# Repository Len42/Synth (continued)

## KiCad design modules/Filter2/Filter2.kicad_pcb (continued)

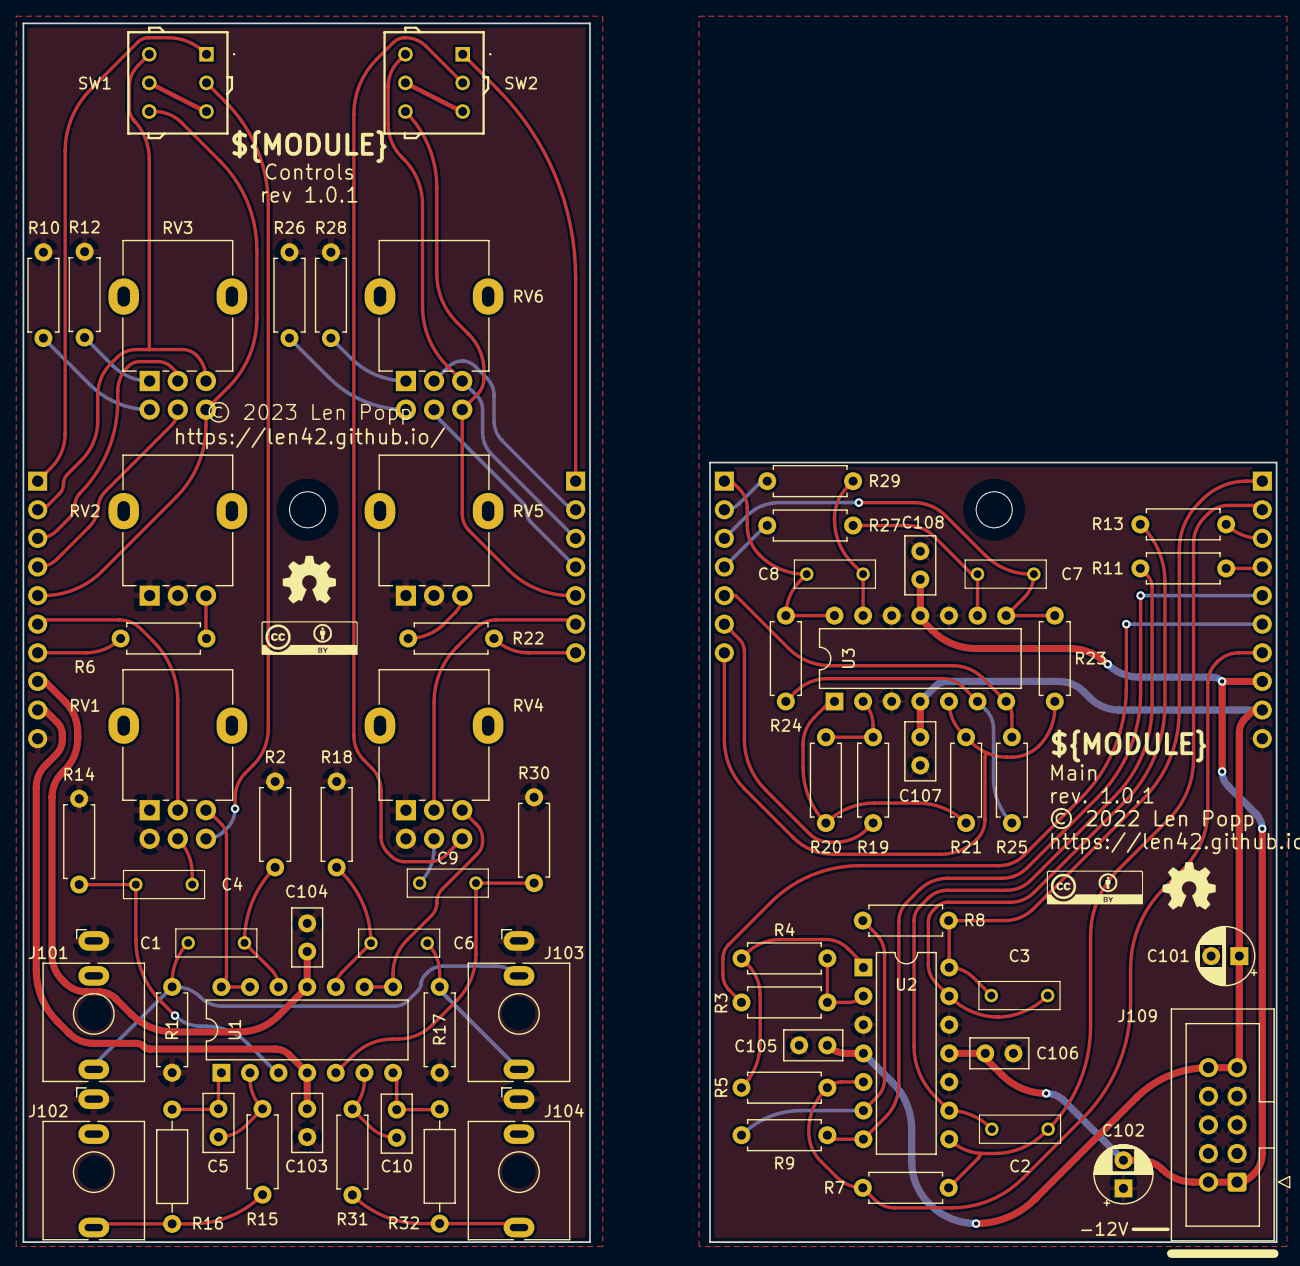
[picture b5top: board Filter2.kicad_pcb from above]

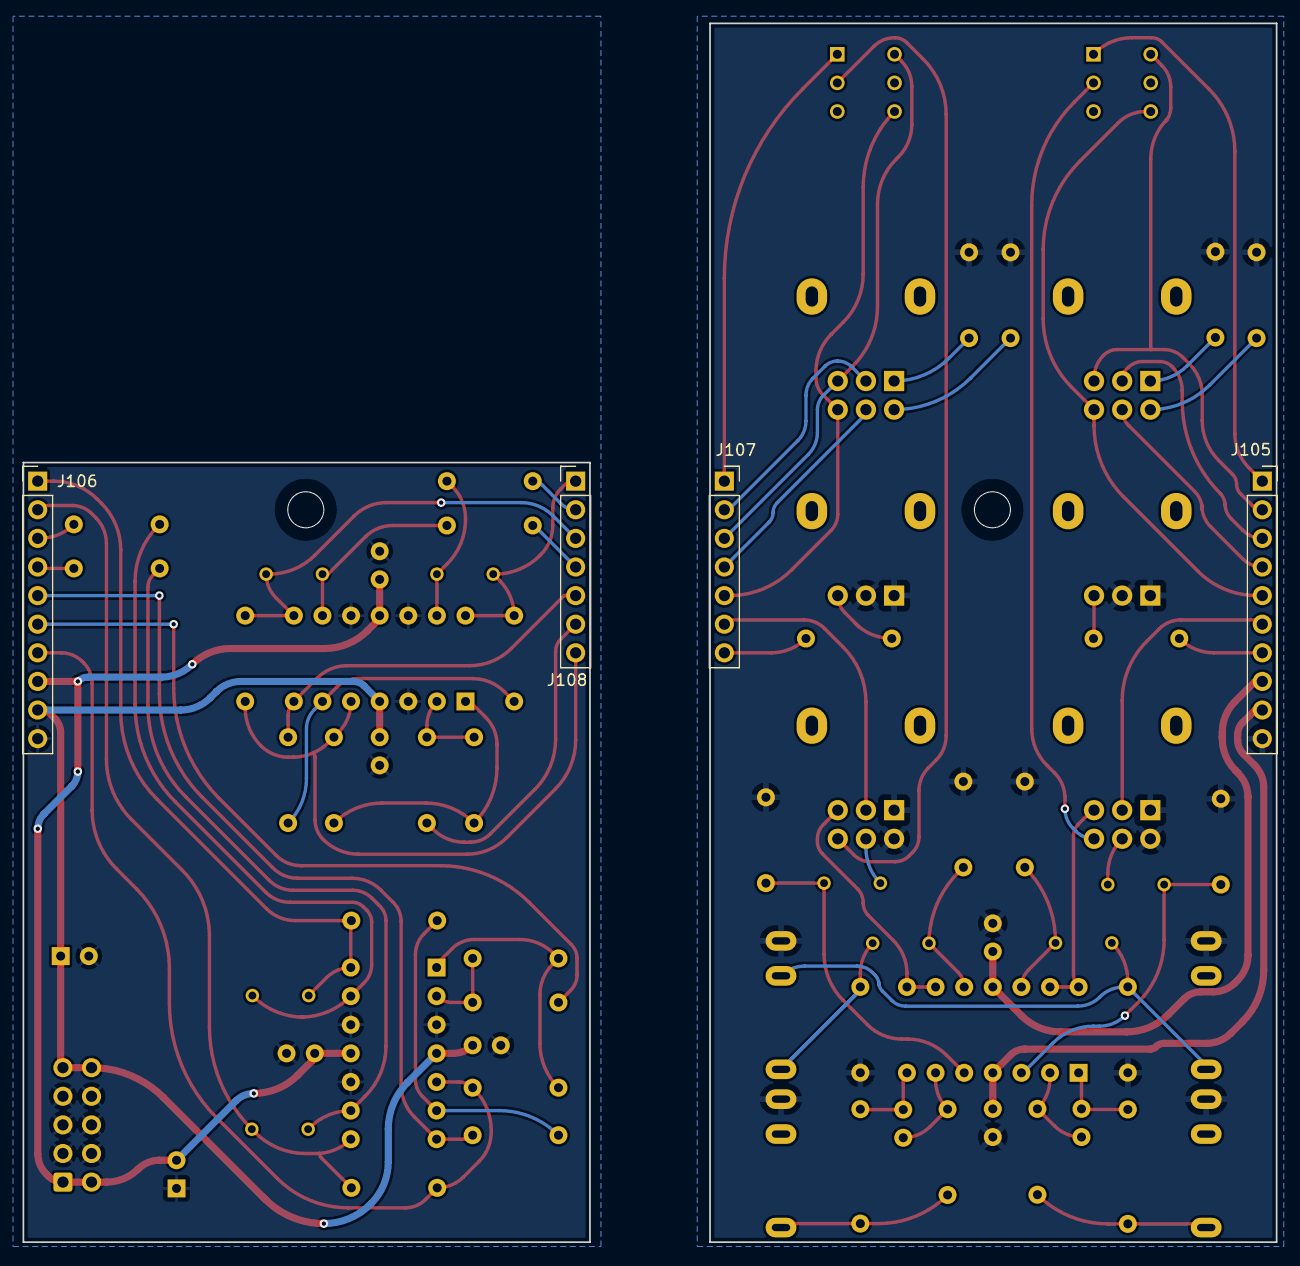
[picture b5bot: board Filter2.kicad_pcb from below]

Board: 2 copper layers, 111.3 x 108.2 mm, 76 parts (4 on the bottom side), 51 nets.

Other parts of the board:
G1, G2: Logo_CC_BY
G3, G4: Logo_OSHW

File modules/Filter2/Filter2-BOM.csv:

Ref,Qty,Value,Value2,Note,Description,Datasheet,Manufacturer,ManuPartNum,Distributor1,DistributorPartNum1,DistributorPartLink1,Distributor2,DistributorPartNum2,DistributorPartLink2,Distributor3,DistributorPartNum3,DistributorPartLink3
"A101","1","Cable_Eurorack_10","","Length as required","Eurorack 16-10 pin power cable","","","","Thonk","","https://www.thonk.co.uk/shop/eurorack-power-cables/","SynthCube","","https://synthcube.com/cart/eurorack-ribbon-power-cables","Modular Addict","","https://modularaddict.com/parts/eurorack-power-cables-1"
"C1 C4 C6 C9","4","1U","","","Capacitor - Film","https://www.mouser.ca/datasheet/2/447/KEM_F3101_R82-3316969.pdf","KEMET","R82DC4100AA60K","Mouser","80-R82DC4100AA60K","https://www.mouser.ca/ProductDetail/KEMET/R82DC4100AA60K?qs=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","","","","","",""
"C2 C3 C7 C8","4","2N2","","","Capacitor - Film","https://www.mouser.ca/datasheet/2/447/F3294_MMK-3316041.pdf","KEMET","MMK5222J100J01L16.5TA18","Mouser","80-MMK5222J100J1TA18","https://www.mouser.ca/ProductDetail/KEMET/MMK5222J100J01L16.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","","","","","",""
"C5 C10","2","22P","C0G","","Capacitor - Ceramic","https://product.tdk.com/system/files/dam/doc/product/capacit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","TDK","FG18C0G1H220JNT00","Mouser","810-FG18C0G1H220JNT0","https://www.mouser.ca/ProductDetail/TDK/FG18C0G1H220JNT00?qs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","","","","","",""
"C101 C102","2","10U","35 VDC","12 V decoupling","Capacitor - Electrolytic - 12 V decoupling","https://www.mouser.ca/datasheet/2/315/ABA0000C1059-947582.pdf","Panasonic","ECE-A1VKS100I","Mouser","667-ECE-A1VKS100I","https://www.mouser.ca/ProductDetail/667-ECE-A1VKS100I","Thonk","Group_Eurorack_DIY_Essential","https://www.thonk.co.uk/shop/eurorack-diy-essentials/","","",""
"C103 C104 C105 C106 C107 C108","6","100N","","IC decoupling","Capacitor - Ceramic - IC decoupling","https://product.tdk.com/system/files/dam/doc/product/capacit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","TDK","FG18X7R1H104KNT06","Mouser","810-FG18X7R1H104KNT6","https://www.mouser.ca/ProductDetail/810-FG18X7R1H104KNT6","","","","","",""
"H101 H105","2","HW_Screw_M3x0.50x6","","","Machine screw, M3x0.50x6","","","","","","","","","","","",""
"H103","1","HW_Standoff_F-F_11mm_M3x0.50","","","Standoff, 11mm, female-female, M3x0.50","https://www.thonk.co.uk/wp-content/uploads/2018/05/standoff-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","Ettinger","05.03.111","Thonk","Mech_11mm_Standoff_(x10)","https://www.thonk.co.uk/shop/standoffs/","Mouser","710-970110321","https://www.mouser.ca/ProductDetail/Wurth-Elektronik/9701103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","Mouser","144-MTS-11","https://www.mouser.ca/ProductDetail/144-MTS-11"
"J101 J102 J103 J104","4","WQP-PJ398","","","Audio Jack, 2 Poles (Mono / TS), Switched T Pole (Normalling), QingPu / Thonkiconn","http://www.qingpu-electronics.com/en/products/WQP-PJ398SM-362.html","QingPu / Thonk","PJ398SM / WQP518MA","Thonk","PJ398SM","https://www.thonk.co.uk/shop/thonkiconn/","SynthCube","WQP518MA","https://synthcube.com/cart/3-5mm-euro-jacks","Adafruit","4031","https://www.adafruit.com/product/4031"
"J105","1","Conn_Front_Left_Top","","","Generic connector, single row, 01x10, script generated (kicad-library-utils/schlib/autogen/connector/)","","","","Adafruit","598","https://www.adafruit.com/product/598","Mouser","710-61303211821","https://www.mouser.ca/ProductDetail/Wurth-Elektronik/6130321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","","",""
"J106","1","Conn_Back_Right_Top","","","Generic connector, single row, 01x10, script generated (kicad-library-utils/schlib/autogen/connector/)","","","","Adafruit","392","https://www.adafruit.com/product/392","Mouser","649-1012937893601BLF","https://www.mouser.ca/ProductDetail/649-1012937893601BLF","","",""
"J107","1","Conn_Front_Right","","","Generic connector, single row, 01x07, script generated (kicad-library-utils/schlib/autogen/connector/)","","","","Adafruit","598","https://www.adafruit.com/product/598","Mouser","710-61303211821","https://www.mouser.ca/ProductDetail/Wurth-Elektronik/6130321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","","",""
"J108","1","Conn_Back_Left","","","Generic connector, single row, 01x07, script generated (kicad-library-utils/schlib/autogen/connector/)","","","","Adafruit","392","https://www.adafruit.com/product/392","Mouser","649-1012937893601BLF","https://www.mouser.ca/ProductDetail/649-1012937893601BLF","","",""
"J109","1","Conn_Eurorack_10","","","Eurorack 10-pin board power connector","https://www.mouser.ca/datasheet/2/445/61201021621-1717731.pdf","Wurth Elektronik","61201021621","Mouser","710-61201021621","https://www.mouser.ca/ProductDetail/Wurth-Elektronik/6120102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","Thonk","","https://www.thonk.co.uk/shop/eurorack-diy-essentials/","","",""
"R1 R14 R17 R30","4","1M","1%, 1/6 W","","Resistor","https://www.mouser.ca/datasheet/2/447/YAGEO_MFR_datasheet_20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","YAGEO","MFR-12FTF52-1M","Mouser","603-MFR-12FTF52-1M","https://www.mouser.ca/ProductDetail/YAGEO/MFR-12FTF52-1M?qs=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","","","","","",""
"R2 R15 R18 R31","4","100K","1%, 1/6 W","","Resistor","https://www.mouser.ca/datasheet/2/447/YAGEO_MFR_datasheet_20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","YAGEO","MFR-12FTF52-100K","Mouser","603-MFR-12FTF52-100K","https://www.mouser.ca/ProductDetail/YAGEO/MFR-12FTF52-100K?q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","","","","","",""
"R3 R7 R11 R13 R19 R23 R27 R29","8","10K","1%, 1/6 W","","Resistor","https://www.mouser.ca/datasheet/2/447/YAGEO_MFR_datasheet_20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","YAGEO","MFR-12FTF52-10K","Mouser","603-MFR-12FTF52-10K","https://www.mouser.ca/ProductDetail/YAGEO/MFR-12FTF52-10K?qs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","","","","","",""
"R4 R5 R20 R21","4","22K","1%, 1/6 W","","Resistor","https://www.mouser.ca/datasheet/2/447/YAGEO_MFR_datasheet_20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","YAGEO","MFR-12FTF52-22K","Mouser","603-MFR-12FTF52-22K","https://www.mouser.ca/ProductDetail/YAGEO/MFR-12FTF52-22K?qs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","","","","","",""
"R6 R22","2","1K","1%, 1/6 W","","Resistor","https://www.mouser.ca/datasheet/2/447/YAGEO_MFR_datasheet_20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","YAGEO","MFR-12FTF52-1K","Mouser","603-MFR-12FTF52-1K","https://www.mouser.ca/ProductDetail/YAGEO/MFR-12FTF52-1K?qs=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","","","","","",""
"R8 R9 R24 R25","4","15K","1%, 1/6 W","","Resistor","https://www.mouser.ca/datasheet/2/447/YAGEO_MFR_datasheet_20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","YAGEO","MFR-12FTF52-15K","Mouser","603-MFR-12FTF52-15K","https://www.mouser.ca/ProductDetail/YAGEO/MFR-12FTF52-15K?qs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","","","","","",""
"R10 R12 R26 R28","4","68R","1%, 1/6 W","","Resistor","https://www.mouser.ca/datasheet/2/447/YAGEO_MFR_datasheet_20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","YAGEO","MFR-12FTF52-68R","Mouser","603-MFR-12FTF52-68R","https://www.mouser.ca/ProductDetail/YAGEO/MFR-12FTF52-68R?qs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","","","","","",""
"R16 R32","2","51R","1%, 1/4 W","Output limiting","Resistor","https://www.mouser.ca/datasheet/2/447/Yageo_LR_MFR_1-1714151.pdf","YAGEO","MFR-25FBF52-51R","Mouser","603-MFR-25FBF52-51R","https://www.mouser.ca/ProductDetail/?qs=oAGoVhmvjhzVx2bdEH1T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","","","","","",""
"RV1 RV4","2","50K","LOG","","Dual potentiometer, separate units","https://www.thonk.co.uk/wp-content/uploads/Documents/alpha/9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","Alpha","RD902F-*","Thonk","Group_Pot_Alpha_6.35mm","https://www.thonk.co.uk/shop/alpha-9mm-pots/","","","","","",""
"RV2 RV5","2","50K","LOG","","Potentiometer","https://www.mouser.ca/datasheet/2/13/alpha_taiwan_08192019_R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","Alpha","RD901F-*","Thonk","Group_Pot_Alpha_6.35mm","https://www.thonk.co.uk/shop/alpha-9mm-pots/","","","","","",""
"RV3 RV6","2","10K","LOG","","Dual potentiometer, separate units","https://www.thonk.co.uk/wp-content/uploads/Documents/alpha/9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","Alpha","RD902F-*","Thonk","Group_Pot_Alpha_6.35mm","https://www.thonk.co.uk/shop/alpha-9mm-pots/","","","","","",""
"SW1 SW2","2","SW_SP3T","","Pins 3 & 5 must be connected","Toggle Switch, three position, single pole triple throw, 3 position switch, SP3T, ON-ON-ON, NKK A24JP","https://www.nkkswitches.com/pdf/Atoggles.pdf","NKK","A24JP","Mouser","633-A24JP","https://www.mouser.ca/ProductDetail/NKK-Switches/A24JP?qs=44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","DigiKey","360-3408-ND","https://www.digikey.ca/en/products/detail/nkk-switches/A24JP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","","",""
"U1 U2 U3","3","TL074","","","Quad Low-Noise JFET-Input Operational Amplifiers, DIP-14/SOIC-14","http://www.ti.com/lit/ds/symlink/tl071.pdf","Texas Instruments","TL074BCN","Mouser","595-TL074BCN","https://www.mouser.ca/ProductDetail/?qs=vxEfx8VrU7BHurOY5iQd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","","","","","",""

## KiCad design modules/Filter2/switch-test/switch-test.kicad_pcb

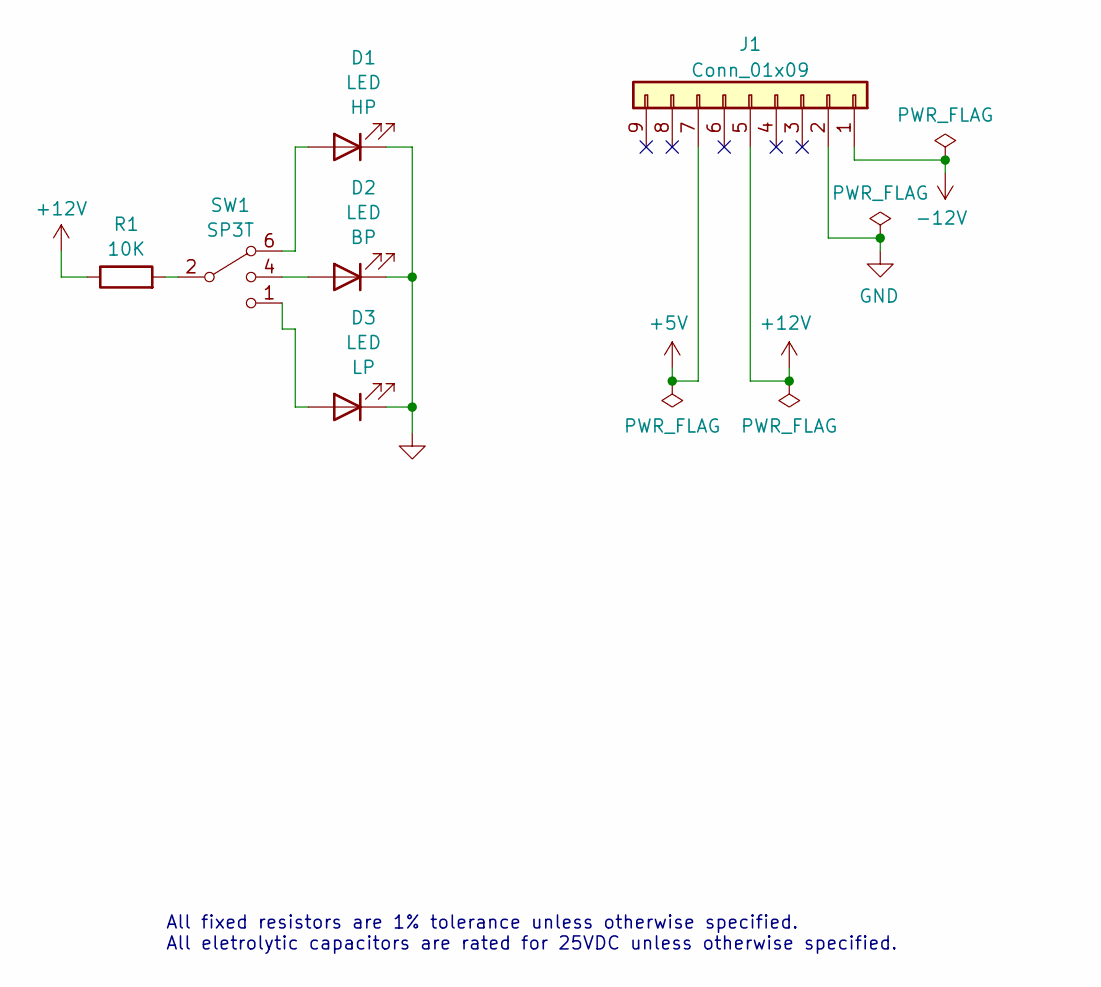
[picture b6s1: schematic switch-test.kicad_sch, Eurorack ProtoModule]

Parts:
D1, D2, D3: LED; LED_D3.0mm_Clear
J1: Conn_01x09; PinHeader_1x09_P2.54mm_Vertical
R1: 10K; SB_Gen_1; ManufacturerPartNum MFR-12*
SW1: SP3T; SW_SP3T_A24JP; ManufacturerPartNum A24JP

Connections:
+5V: J1.7
+12V: J1.5, R1.1
-12V: J1.1
GND: D1.1 (K), D2.1 (K), D3.1 (K), J1.2
unnamed: D1.2 (A), SW1.6
unnamed: D2.2 (A), SW1.4
unnamed: D3.2 (A), SW1.1
unnamed: R1.2, SW1.2

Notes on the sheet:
All fixed resistors are 1% tolerance unless otherwise specified. All eletrolytic capacitors are rated for 25VDC unless otherwise specified.

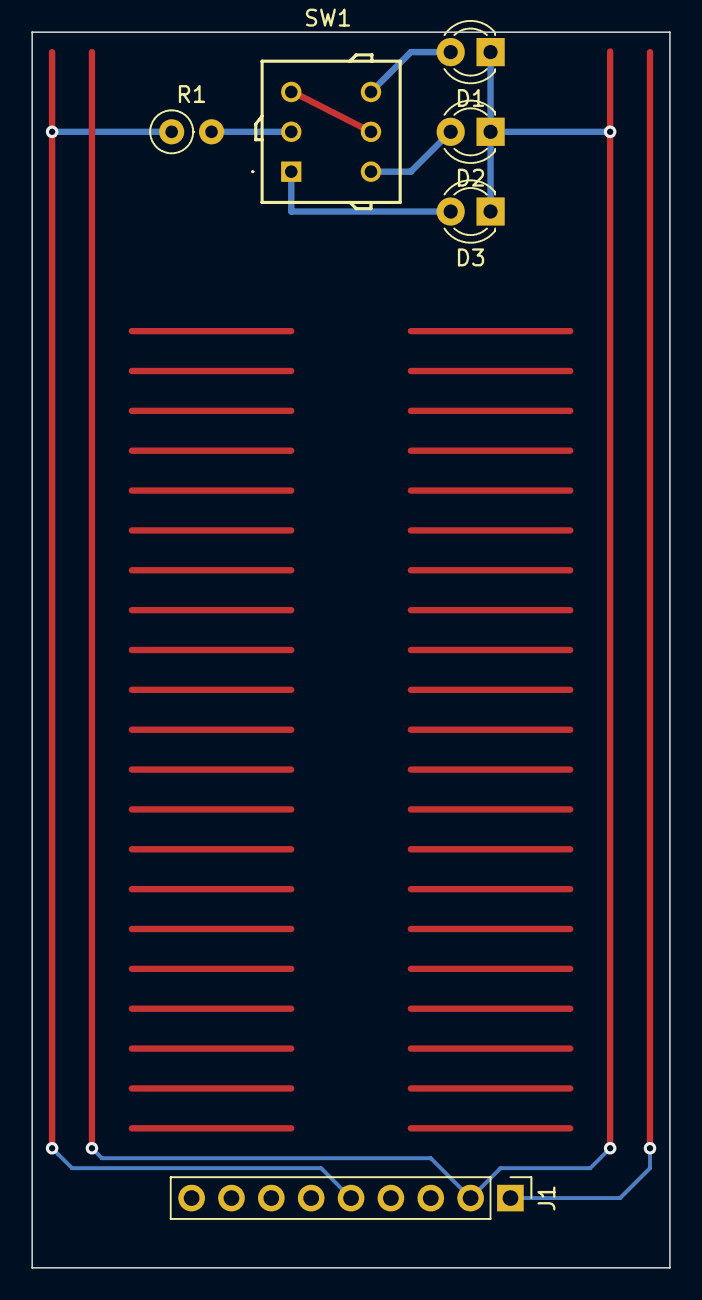
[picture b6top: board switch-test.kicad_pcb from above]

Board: 6 copper layers, 40.6 x 78.7 mm, 6 parts (0 on the bottom side), 6 nets.

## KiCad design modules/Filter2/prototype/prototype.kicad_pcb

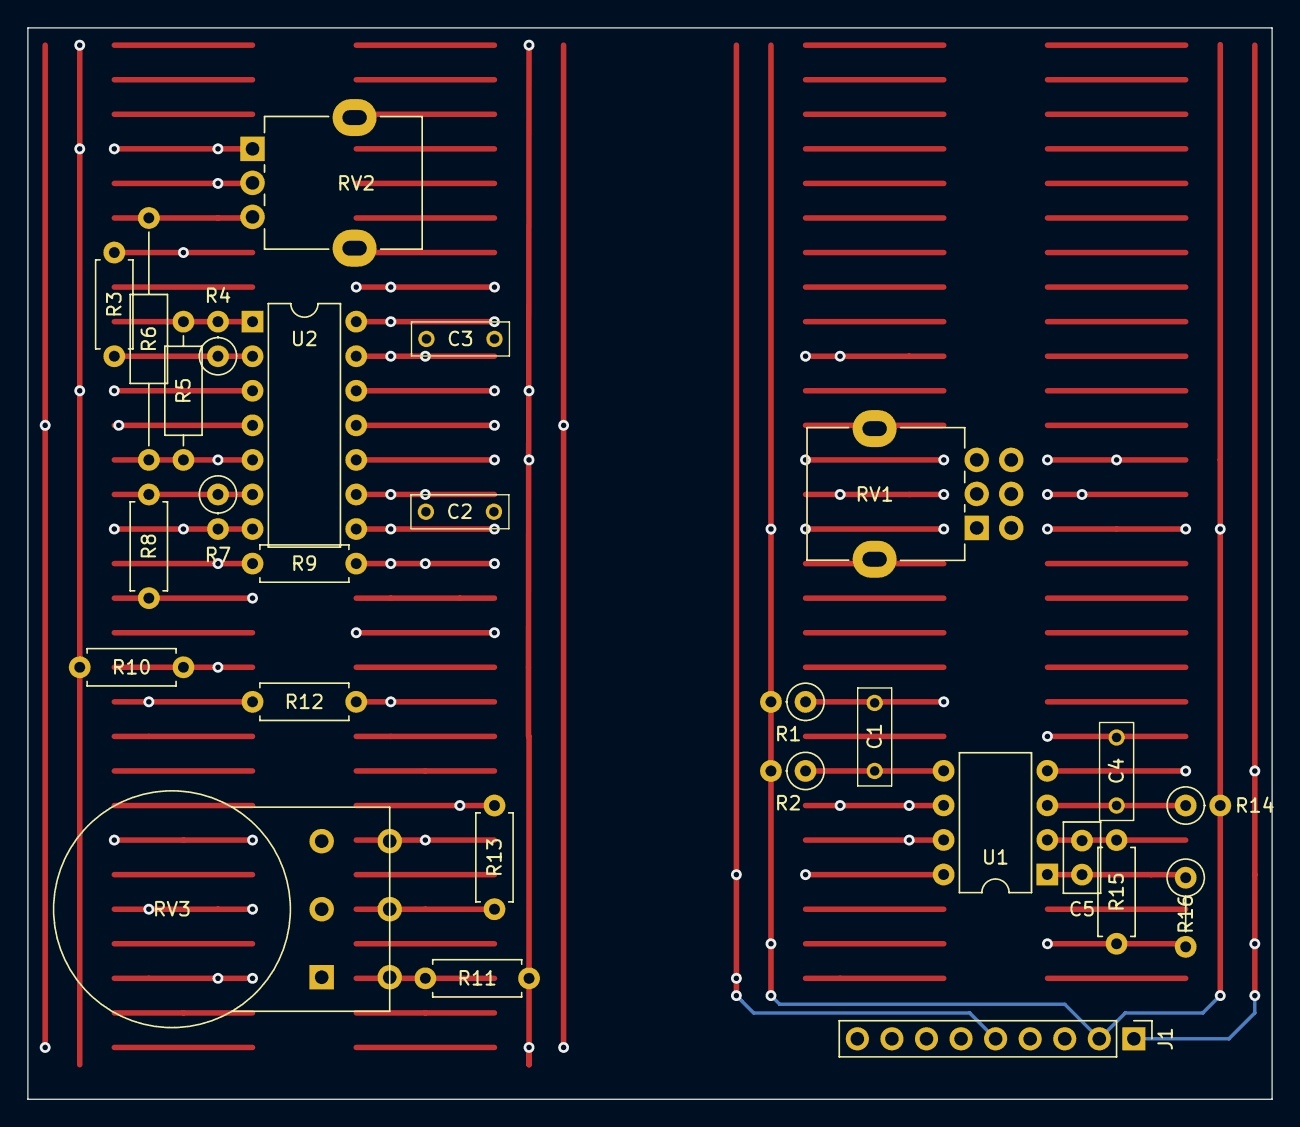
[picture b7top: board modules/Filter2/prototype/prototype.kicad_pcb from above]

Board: 6 copper layers, 91.4 x 78.7 mm, 27 parts (0 on the bottom side), 26 nets.

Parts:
C1, C4: 1U; C_Rect_Kemet_L7.2mm_W2.5mm_P5mm
C2, C3: 1N2; C_Rect_Kemet_L7.2mm_W2.5mm_P5mm
C5: 22P; C_Disc_D5.0mm_W2.5mm_P2.50mm
J1: Conn_01x09; PinHeader_1x09_P2.54mm_Vertical
R1, R14: 1M; SB_Gen_1
R2: 100K; SB_Gen_1
R3, R9: 10K; R_Axial_DIN0207_L6.3mm_D2.5mm_P7.62mm_Horizontal
R4: 22K; SB_Gen_1
R5: 22K; SB_Gen_4
R6: 1K; SB_Gen_7
R7: 15K; SB_Gen_1
R8, R12, R13: 15K; R_Axial_DIN0207_L6.3mm_D2.5mm_P7.62mm_Horizontal
R10, R11: 51R; R_Axial_DIN0207_L6.3mm_D2.5mm_P7.62mm_Horizontal
R15: 100K; R_Axial_DIN0207_L6.3mm_D2.5mm_P7.62mm_Horizontal
R16: 51R; SB_Gen_2
RV1: 50K; Potentiometer_Alpha_RD902F-40-00D_Dual_Vertical
RV2: 50K; Potentiometer_Alpha_RD901F-40-00D_Single_Vertical
RV3: 10K; Potentiometer_Alpha_RV16A01F_Dual_Vertical_NoTab
U1: TL072; DIP-8_W7.62mm
U2: TL074; DIP-14_W7.62mm

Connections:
+12V: J1.5, U1.8 (V+), U2.4 (V+)
-12V: J1.1, U1.4 (V-), U2.11 (V-)
BP: C2.2, R9.2, RV1.6, RV3.6, U2.8
FILTER-IN: R3.1, RV1.2
GND: J1.2, R1.2, R2.2, R10.1, R11.1, R14.2, RV1.1, RV1.4, RV2.1, RV2.2, U2.3 (+), U2.10 (+), U2.12 (+)
HP: R7.2, RV3.3, U2.7
IN: C1.1, J1.4, R1.1
LP: C3.2, R8.2, U2.14
unnamed: C4.1, RV1.5
unnamed: C5.2, R16.1, U1.1
unnamed: R4.2, R5.1, U2.1
unnamed: R6.1, RV2.3
unnamed: R10.2, RV3.1
unnamed: R11.2, RV3.4
unnamed: R12.1, RV3.2
unnamed: R13.1, RV3.5
unnamed: C4.2, R14.1, U1.3 (+)
unnamed: C5.1, R15.1, U1.2 (-)
unnamed: C1.2, R2.1, U1.5 (+)
unnamed: RV1.3, U1.6 (-), U1.7
unnamed: R3.2, R4.1, U2.2 (-)
unnamed: R5.2, R6.2, R9.1, U2.5 (+)
unnamed: R7.1, R8.1, U2.6 (-)
unnamed: C2.1, R12.2, U2.9 (-)
unnamed: C3.1, R13.2, U2.13 (-)
OUT: J1.3, R15.2, R16.2

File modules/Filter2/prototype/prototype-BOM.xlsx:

Ref | Qty | Have | Bought | Need | Value | Value2 | Note | Description | Datasheet | Manufacturer | ManuPartNum | Distributor1 | DistributorPartNum1 | DistributorPartLink1 | Distributor2 | DistributorPartNum2 | DistributorPartLink2 | Distributor3 | DistributorPartNum3 | DistributorPartLink3
C1 C4 | 2 | 2 |  | 0 | 1U |  |  | Capacitor - Film
C2 C3 | 2 | 2 |  | 0 | 1N2 |  |  | Capacitor - Film
C5 | 1 | 1 |  | 0 | 22P | C0G | sub 18PF | Capacitor - Ceramic
C6 C7 C8 C9 | 4 | 4 |  | 0 | 100N |  | IC decoupling | Capacitor - Ceramic - IC decoupling | https://product.tdk.com/system/files/dam/doc/product/capacit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 | TDK | FG18X7R1H104KNT06 | Mouser | 810-FG18X7R1H104KNT6 | https://www.mouser.ca/ProductDetail/810-FG18X7R1H104KNT6
R1 R14 | 2 | 2 |  | 0 | 1M | 1%, 1/6 W |  | Resistor | https://www.mouser.ca/datasheet/2/447/Yageo_LR_MFR_1-1714151.pdf | YAGEO | MFR-12* | Mouser | 603-MFR-12* | https://www.mouser.ca/c/?m=YAGEO&power+rating=166+mW+(1%2f6+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
R2 R15 | 2 | 2 |  | 0 | 100K | 1%, 1/6 W |  | Resistor | https://www.mouser.ca/datasheet/2/447/Yageo_LR_MFR_1-1714151.pdf | YAGEO | MFR-12* | Mouser | 603-MFR-12* | https://www.mouser.ca/c/?m=YAGEO&power+rating=166+mW+(1%2f6+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
R3 R9 | 2 | 4 |  | 0 | 10K | 1%, 1/6 W |  | Resistor | https://www.mouser.ca/datasheet/2/447/Yageo_LR_MFR_1-1714151.pdf | YAGEO | MFR-12* | Mouser | 603-MFR-12* | https://www.mouser.ca/c/?m=YAGEO&power+rating=166+mW+(1%2f6+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
R4 R5 | 2 | 2 |  | 0 | 22K | 1%, 1/6 W |  | Resistor | https://www.mouser.ca/datasheet/2/447/Yageo_LR_MFR_1-1714151.pdf | YAGEO | MFR-12* | Mouser | 603-MFR-12* | https://www.mouser.ca/c/?m=YAGEO&power+rating=166+mW+(1%2f6+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
R6 | 1 | 1 |  | 0 | 1K | 1%, 1/6 W |  | Resistor | https://www.mouser.ca/datasheet/2/447/Yageo_LR_MFR_1-1714151.pdf | YAGEO | MFR-12* | Mouser | 603-MFR-12* | https://www.mouser.ca/c/?m=YAGEO&power+rating=166+mW+(1%2f6+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
R7 R8 R12 R13 | 4 | 4 |  | 0 | 15K | 1%, 1/6 W |  | Resistor | https://www.mouser.ca/datasheet/2/447/Yageo_LR_MFR_1-1714151.pdf | YAGEO | MFR-12* | Mouser | 603-MFR-12* | https://www.mouser.ca/c/?m=YAGEO&power+rating=166+mW+(1%2f6+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
R10 R11 R16 | 3 | 3 |  | 0 | 51R | 1%, 1/4 W | Output limiting | Resistor | https://www.mouser.ca/datasheet/2/447/Yageo_LR_MFR_1-1714151.pdf | YAGEO | MFR-25FBF52-51R | Mouser | 603-MFR-25FBF52-51R | https://www.mouser.ca/ProductDetail/?qs=oAGoVhmvjhzVx2bdEH1T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
RV1 | 1 |  | 3 | 0 | 50K | LOG |  | Dual potentiometer, separate units
RV2 | 1 | 1 |  | 0 | 50K | LOG | sub 100K | Potentiometer | https://www.mouser.ca/datasheet/2/13/alpha_taiwan_08192019_R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 | Alpha | RD901F-* | Thonk | Group_Pot_Alpha_6.35mm | https://www.thonk.co.uk/shop/alpha-9mm-pots/ | Mouser | 311-1940F-* | https://www.mouser.ca/c/passive-components/potentiometers-tr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 | SynthCube | 9MMALPHAPOTMSTR | https://synthcube.com/cart/alpha-9mm-potentiometer-right-ang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
RV3 | 1 |  | 3 | 0 | 10K | LOG |  | Dual potentiometer, separate units
U1 | 1 | 1 |  | 0 | TL072 |  |  | Dual Low-Noise JFET-Input Operational Amplifiers, DIP-8/SOIC-8 | https://www.ti.com/lit/ds/symlink/tl072b.pdf?ts=1628812694194 | Texas Instruments | TL072BCP | Mouser | 595-TL072BCP | https://www.mouser.ca/ProductDetail/Texas-Instruments/TL072B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
U2 | 1 | 1 |  | 0 | TL074 |  |  | Quad Low-Noise JFET-Input Operational Amplifiers, DIP-14/SOIC-14 | http://www.ti.com/lit/ds/symlink/tl071.pdf | Texas Instruments | TL074BCN | Mouser | 595-TL074BCN | https://www.mouser.ca/ProductDetail/?qs=vxEfx8VrU7BHurOY5iQd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

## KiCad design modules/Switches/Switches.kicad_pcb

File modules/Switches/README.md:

# Switches

## 8HP Eurorack Module

_4-channel muting module_

### Features
- 4 channels with individual mute switches
- Light-touch pushbuttons that light up when a channel is "on"
- JFET "soft switching" for click-free muting
- Each input is normalled to the next one

### Notes
Due to the JFET cut-off voltage, signals below approx. -8 V are not passed through. This does not affect "normal" audio or CV signals, but an over-driven audio signal may be clipped or an extremely negative CV may be altered.

This module requires a 16-pin Eurorack power cable that supplies +5 V power in addition to +12 V and -12 V.

PCB layouts are provided in KiCad and gerber formats. A PCB layout for a drilled front panel (with no labels) is also included.

The PCBs that I used can be ordered from OSH Park. The designs are here:
- [Main board](https://oshpark.com/shared_projects/p9aatPIx)
- [Controls board](https://oshpark.com/shared_projects/ahwXdaiJ)
- [Front panel](https://oshpark.com/shared_projects/iH5W0M5Z)

Please note that I am a hobbyist, not a trained electronics engineer. No guarantees!

### Acknowledgements
This design is based in part on [a circuit by Rod Elliott](http://sound-au.com/articles/muting.html#s2).

### Software Used

* [KiCad](https://www.kicad.org/) 7.0.8

<hr /><div><div style="float:left; padding-right:10px;"></div><div style="xfloat:left; padding-left:10px;"><br />© 2023 Len Popp CC BY<br />This work is licensed under a <a rel="license" href="http://creativecommons.org/licenses/by/4.0/">Creative Commons Attribution 4.0 International License</a>.</div></div>

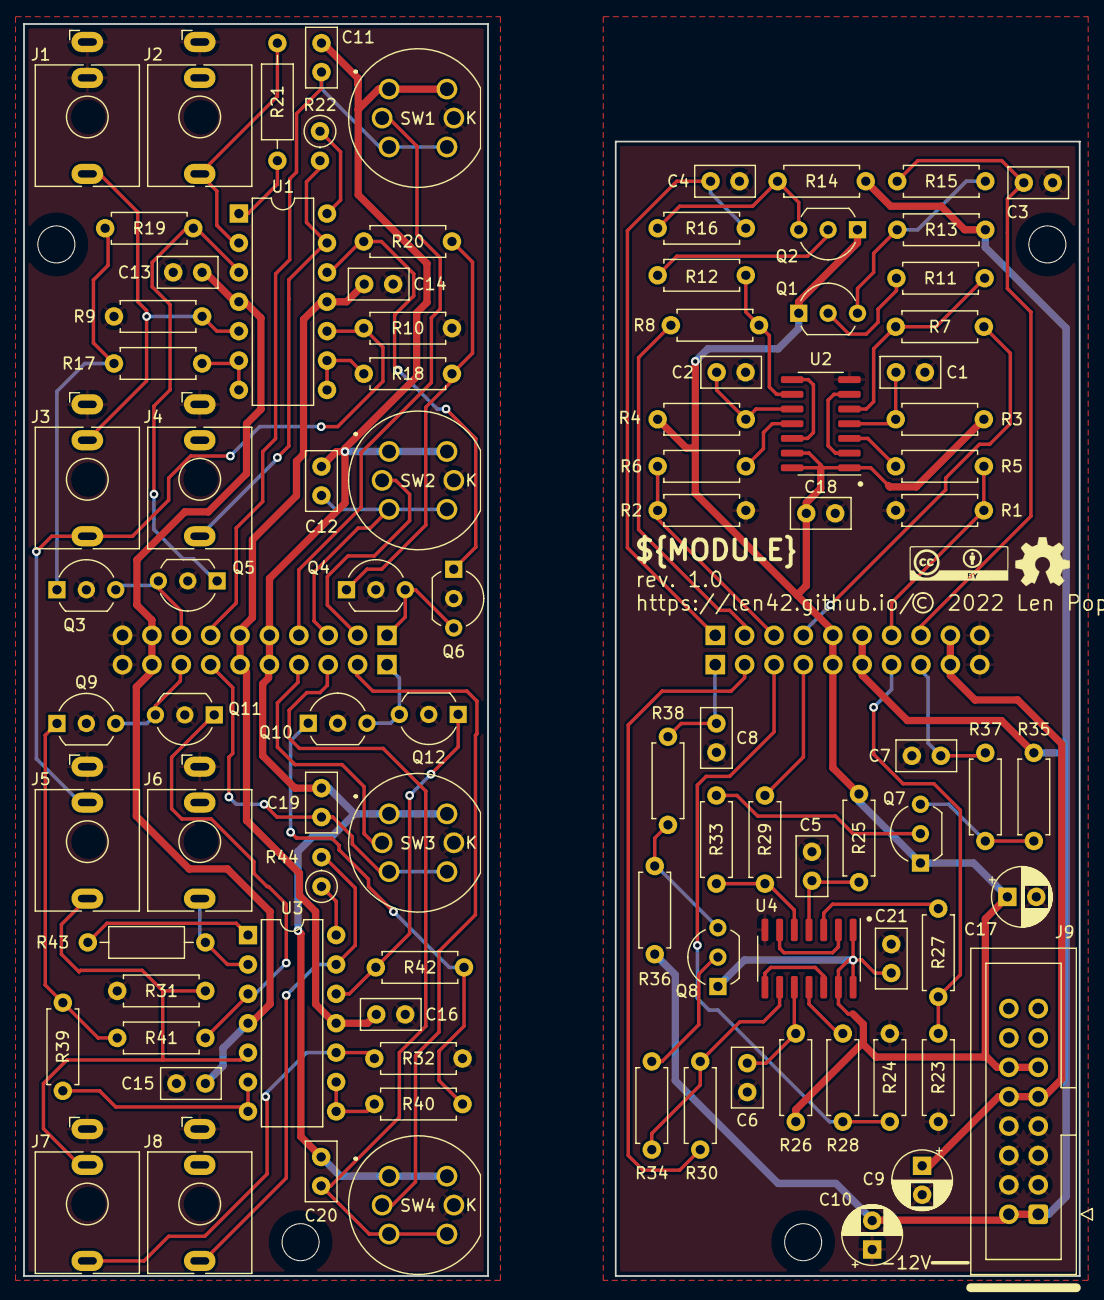
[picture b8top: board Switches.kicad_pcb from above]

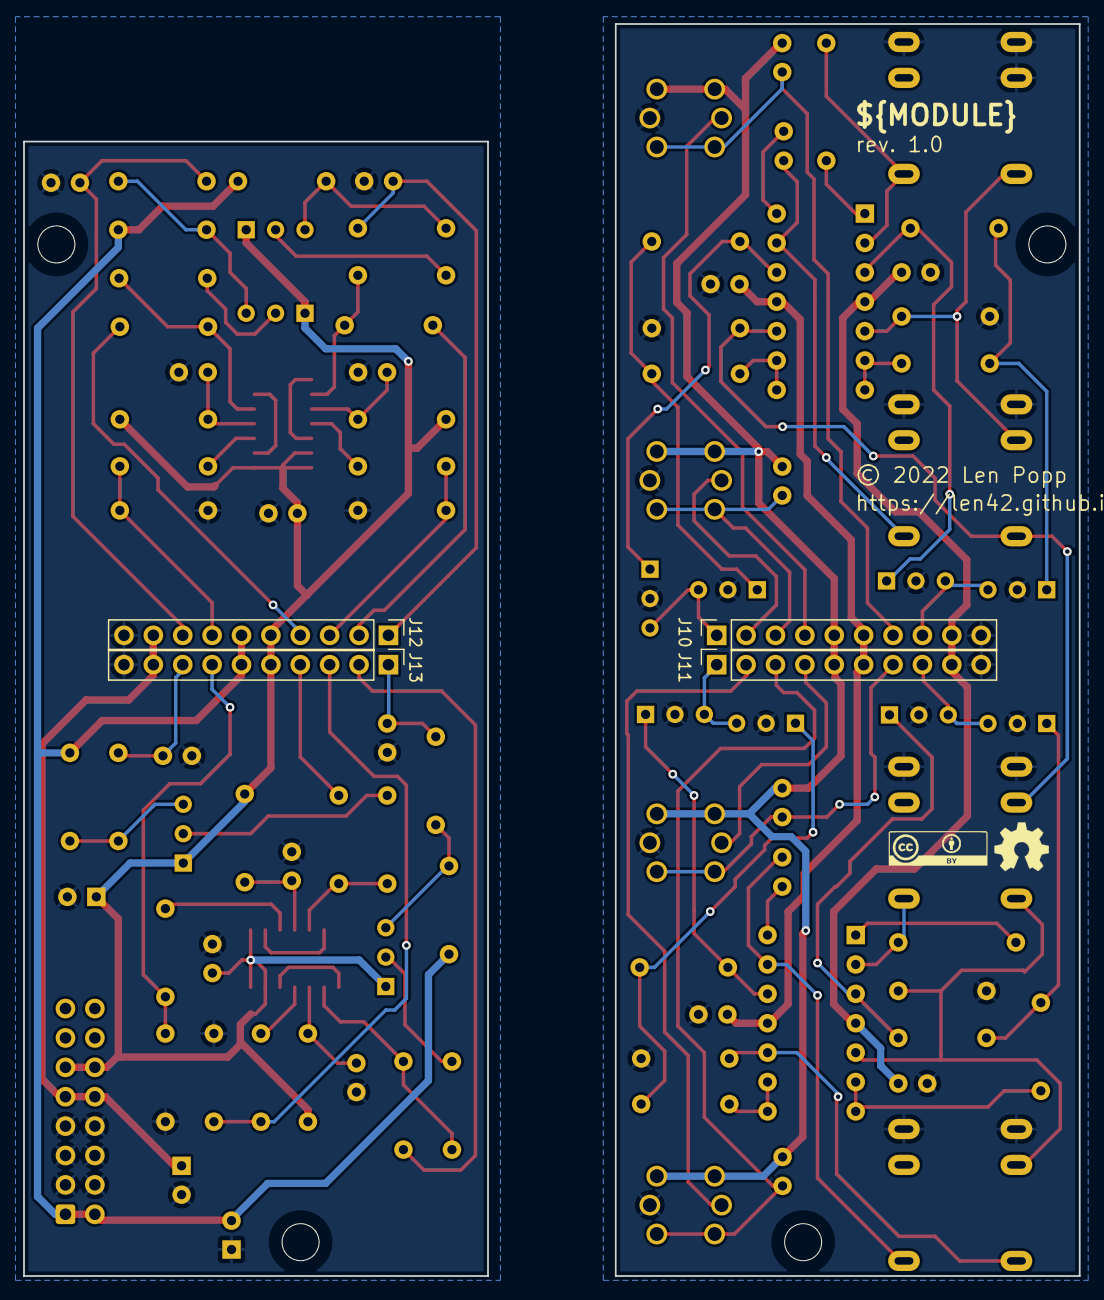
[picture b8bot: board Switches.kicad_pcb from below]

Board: 2 copper layers, 91.2 x 108.2 mm, 106 parts (6 on the bottom side), 64 nets.

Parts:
C1, C2, C3, C4, C5, C6, C7, C8, C13, C14, C15, C16, C18, C21: 100N; C_Disc_D5.0mm_W2.5mm_P2.50mm
C9, C10, C17: 10U; CP_Radial_D5.0mm_P2.50mm
C11, C12, C19, C20: 1N; C_Disc_D5.0mm_W2.5mm_P2.50mm
G1, G6: Logo_CC_BY
G3, G5: Logo_OSHW
H2, H4, H7, H9: MountingHole_M3; MountingHole_PCB_3.2mm_M3
J1, J2, J3, J4, J5, J6, J7, J8: WQP-PJ398; Jack_3.5mm_QingPu_WQP-PJ398SM_Vertical
J9: Conn_Eurorack_16; IDC-Header-Eurorack-16-TH
J10: Conn_Front_Top; PinSocket_1x10_P2.54mm_Vertical
J11: Conn_Front_Bottom; PinSocket_1x10_P2.54mm_Vertical
J12: Conn_Back_Top; PinHeader_1x10_P2.54mm_Vertical
J13: Conn_Back_Bottom; PinHeader_1x10_P2.54mm_Vertical
Q1, Q2, Q7, Q8: 2N3906; TO-92_Inline_Wide
Q3, Q4, Q5, Q6, Q9, Q10, Q11, Q12: J109; TO-92_Inline_Wide
R1, R2, R3, R4, R11, R12, R13, R14, R17, R18, R19, R20, R23, R24, R25, R26, R33, R34, R35, R36, R39, R40, R41, R42: 10K; R_Axial_DIN0207_L6.3mm_D2.5mm_P7.62mm_Horizontal
R5, R6, R27, R28: 1K; R_Axial_DIN0207_L6.3mm_D2.5mm_P7.62mm_Horizontal
R7, R8, R29, R30: 330R; R_Axial_DIN0207_L6.3mm_D2.5mm_P7.62mm_Horizontal
R9, R10, R31, R32: 100k; R_Axial_DIN0207_L6.3mm_D2.5mm_P7.62mm_Horizontal
R15, R16, R37, R38: 240K; R_Axial_DIN0207_L6.3mm_D2.5mm_P7.62mm_Horizontal
R21, R43: 1K; R_Axial_DIN0207_L6.3mm_D2.5mm_P10.16mm_Horizontal
R22, R44: 1K; SB_Gen_1
SW1, SW2, SW3, SW4: D6RLxxF1; SW_Push_LED_C&K_D6R
U1, U3: TL074; DIP-14_W7.62mm
U2, U4: SN74HCS74; SOIC-14_3.9x8.7mm_P1.27mm

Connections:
+5V: C11.1, C12.1, C17.1, C18.1, C19.1, C20.1, C21.1, J9.11 (+5V), J9.12, J10.5, J11.5, J12.5, J13.5, Q1.1 (E), Q2.1 (E), Q7.1 (E), Q8.1 (E), R3.1, R4.1, R25.1, R26.1, SW1.1, SW1.2, SW2.1, SW2.2, SW3.1, SW3.2, SW4.1, SW4.2, U2.1 (~R), U2.13 (~R), U2.14 (VDD), U4.1 (~R), U4.13 (~R), U4.14 (VDD)
+12V: C9.1, C13.1, C15.1, J9.9 (+12V), J9.10, J10.9, J11.9, J12.9, J13.9, U1.4 (V+), U3.4 (V+)
-12V: C10.2, C14.2, C16.2, J9.1 (-12V), J9.2, J10.6, J11.6, J12.6, J13.6, R13.2, R14.2, R35.2, R36.2, U1.11 (V-), U3.11 (V-)
GND: C1.2, C2.2, C3.2, C4.2, C5.2, C6.2, C7.2, C8.2, C9.2, C10.1, C13.2, C14.1, C15.2, C16.1, C17.2, C18.2, C21.2, J1.S, J1.TN, J2.S, J3.S, J4.S, J5.S, J6.S, J7.S, J8.S, J9.3 (GND), J9.4, J9.5 (GND), J9.6, J9.7 (GND), J9.8, J10.10, J11.10, J12.10, J13.10, Q3.2 (S), Q4.2 (S), Q5.2 (S), Q6.2 (S), Q9.2 (S), Q10.2 (S), Q11.2 (S), Q12.2 (S), R1.2, R2.2, R9.1, R10.1, R23.2, R24.2, R31.1, R32.1, SW1.6 (K), SW2.6 (K), SW3.6 (K), SW4.6 (K), U2.7 (VSS), U4.7 (VSS)
IN-1: J1.T, J3.TN, R9.2, U1.5 (+)
IN-2: J3.T, J5.TN, R10.2, U1.10 (+)
IN-3: J5.T, J7.TN, R31.2, U3.5 (+)
IN-4: J7.T, R32.2, U3.10 (+)
LED-1: J10.4, J12.4, R7.2, SW1.5 (A)
LED-2: J10.2, J12.2, R8.2, SW2.5 (A)
LED-3: J11.4, J13.4, R29.2, SW3.5 (A)
LED-4: J11.2, J13.2, R30.2, SW4.5 (A)
MUTE-1: C3.1, J10.8, J12.8, Q3.3 (G), Q5.3 (G), R15.2
MUTE-2: C4.1, J10.1, J12.1, Q4.3 (G), Q6.3 (G), R16.2
MUTE-3: C7.1, J11.8, J13.8, Q9.3 (G), Q11.3 (G), R37.2
MUTE-4: C8.1, J11.1, J13.1, Q10.3 (G), Q12.3 (G), R38.2
unnamed: Q1.2 (B), R11.2
unnamed: Q1.3 (C), R13.1, R15.1
unnamed: Q2.2 (B), R12.2
unnamed: Q2.3 (C), R14.1, R16.1
unnamed: Q3.1 (D), R17.2, R19.1
unnamed: Q4.1 (D), R18.2, R20.1
unnamed: Q5.1 (D), R19.2, U1.3 (+)
unnamed: Q6.1 (D), R20.2, U1.12 (+)
unnamed: Q7.2 (B), R33.2
unnamed: Q7.3 (C), R35.1, R37.1
unnamed: Q8.2 (B), R34.2
unnamed: Q8.3 (C), R36.1, R38.1
unnamed: Q9.1 (D), R39.2, R41.1
unnamed: Q10.1 (D), R40.2, R42.1
unnamed: Q11.1 (D), R41.2, U3.3 (+)
unnamed: Q12.1 (D), R42.2, U3.12 (+)
unnamed: R21.1, U1.1
unnamed: R22.1, U1.14
unnamed: R43.1, U3.1
unnamed: R44.1, U3.14
unnamed: R17.1, U1.6 (-), U1.7
unnamed: R18.1, U1.8, U1.9 (-)
unnamed: R5.2, U2.3 (C)
unnamed: U2.2 (D), U2.6 (~Q)
unnamed: R7.1, R11.1, U2.5 (Q)
unnamed: C1.1, R3.2, U2.4 (~S)
unnamed: R6.2, U2.11 (C)
unnamed: U2.8 (~Q), U2.12 (D)
unnamed: R8.1, R12.1, U2.9 (Q)
unnamed: C2.1, R4.2, U2.10 (~S)
unnamed: R39.1, U3.6 (-), U3.7
unnamed: R40.1, U3.8, U3.9 (-)
unnamed: R27.2, U4.3 (C)
unnamed: U4.2 (D), U4.6 (~Q)
unnamed: R29.1, R33.1, U4.5 (Q)
unnamed: C5.1, R25.2, U4.4 (~S)
unnamed: R28.2, U4.11 (C)
unnamed: U4.8 (~Q), U4.12 (D)
unnamed: R30.1, R34.1, U4.9 (Q)
unnamed: C6.1, R26.2, U4.10 (~S)
OUT-1: J2.T, R21.2, U1.2 (-)
OUT-2: J4.T, R22.2, U1.13 (-)
OUT-3: J6.T, R43.2, U3.2 (-)
OUT-4: J8.T, R44.2, U3.13 (-)
SWITCH-1: C11.2, J10.7, J12.7, R1.1, R5.1, SW1.3, SW1.4
SWITCH-2: C12.2, J10.3, J12.3, R2.1, R6.1, SW2.3, SW2.4
SWITCH-3: C19.2, J11.7, J13.7, R23.1, R27.1, SW3.3, SW3.4
SWITCH-4: C20.2, J11.3, J13.3, R24.1, R28.1, SW4.3, SW4.4
